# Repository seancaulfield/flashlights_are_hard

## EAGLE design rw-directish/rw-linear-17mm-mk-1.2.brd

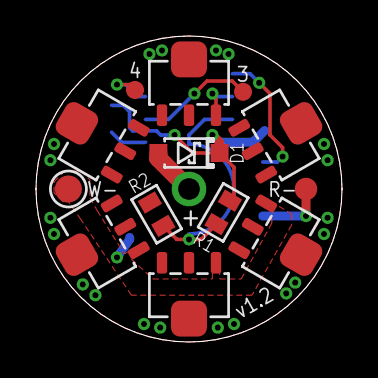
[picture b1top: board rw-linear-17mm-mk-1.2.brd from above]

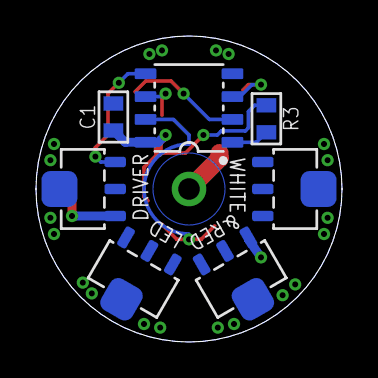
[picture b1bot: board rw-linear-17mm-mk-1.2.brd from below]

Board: 2 copper layers, 17.0 x 17.0 mm, 22 parts (7 on the bottom side), 11 nets.

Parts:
3, 4: M01SMD-1MM-DIA-NS; 1X01-SMD-1MM-DIA-NS
+: M01PTH-1.2MM-NS; 1X01-1.2MM-NS
C1: 1u; C0603-TIGHTER
D1: BAT165; SOD123-SCHOTTKY
FRAME1: FRAME-LETTERNO_PACKAGE; DUMMY
R1: 19K; R0603-TIGHTER
R2: 4K7; R0603-TIGHTER
R3: 10K; R0603-TIGHTER
R-: M01SMD-1.25MM-DIA; 1X01-SMD-1.25MM-DIA-NS
U0: Tiny13; SO08-NARROWER
U1, U2, U3, U4, U5, U6, U7, U8, U9, U10: AMC7135; SOT89-NOTHERM-ROUNDED
W-: M01SMD-1.5MM-DIA-NS; 1X01-SMD-1.5MM-DIA-NS

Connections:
3: 3.P$1, U0.2
4: 4.P$1, U0.3
BATT_DIV: R1.1, R2.2, U0.7
GND: C1.2, R2.1, U0.4, U1.4@1, U1.4@2, U2.4@1, U2.4@2, U3.4@1, U3.4@2, U4.4@1, U4.4@2, U5.4@1, U5.4@2, U6.4@1, U6.4@2, U7.4@1, U7.4@2, U8.4@1, U8.4@2, U9.4@1, U9.4@2, U10.4@1, U10.4@2
unnamed: R3.1, U0.1
PWM_R: U0.5, U10.3
PWM_W: U0.6, U1.3, U2.3, U3.3, U4.3, U5.3, U6.3, U7.3, U8.3, U9.3
RED_K: R-.P$1, U10.1
VBAT: +.P$1, D1.A
VCC: C1.1, D1.C, R1.2, R3.2, U0.8
WHITE_K: U1.1, U2.1, U3.1, U4.1, U5.1, U6.1, U7.1, U8.1, U9.1, W-.P$1

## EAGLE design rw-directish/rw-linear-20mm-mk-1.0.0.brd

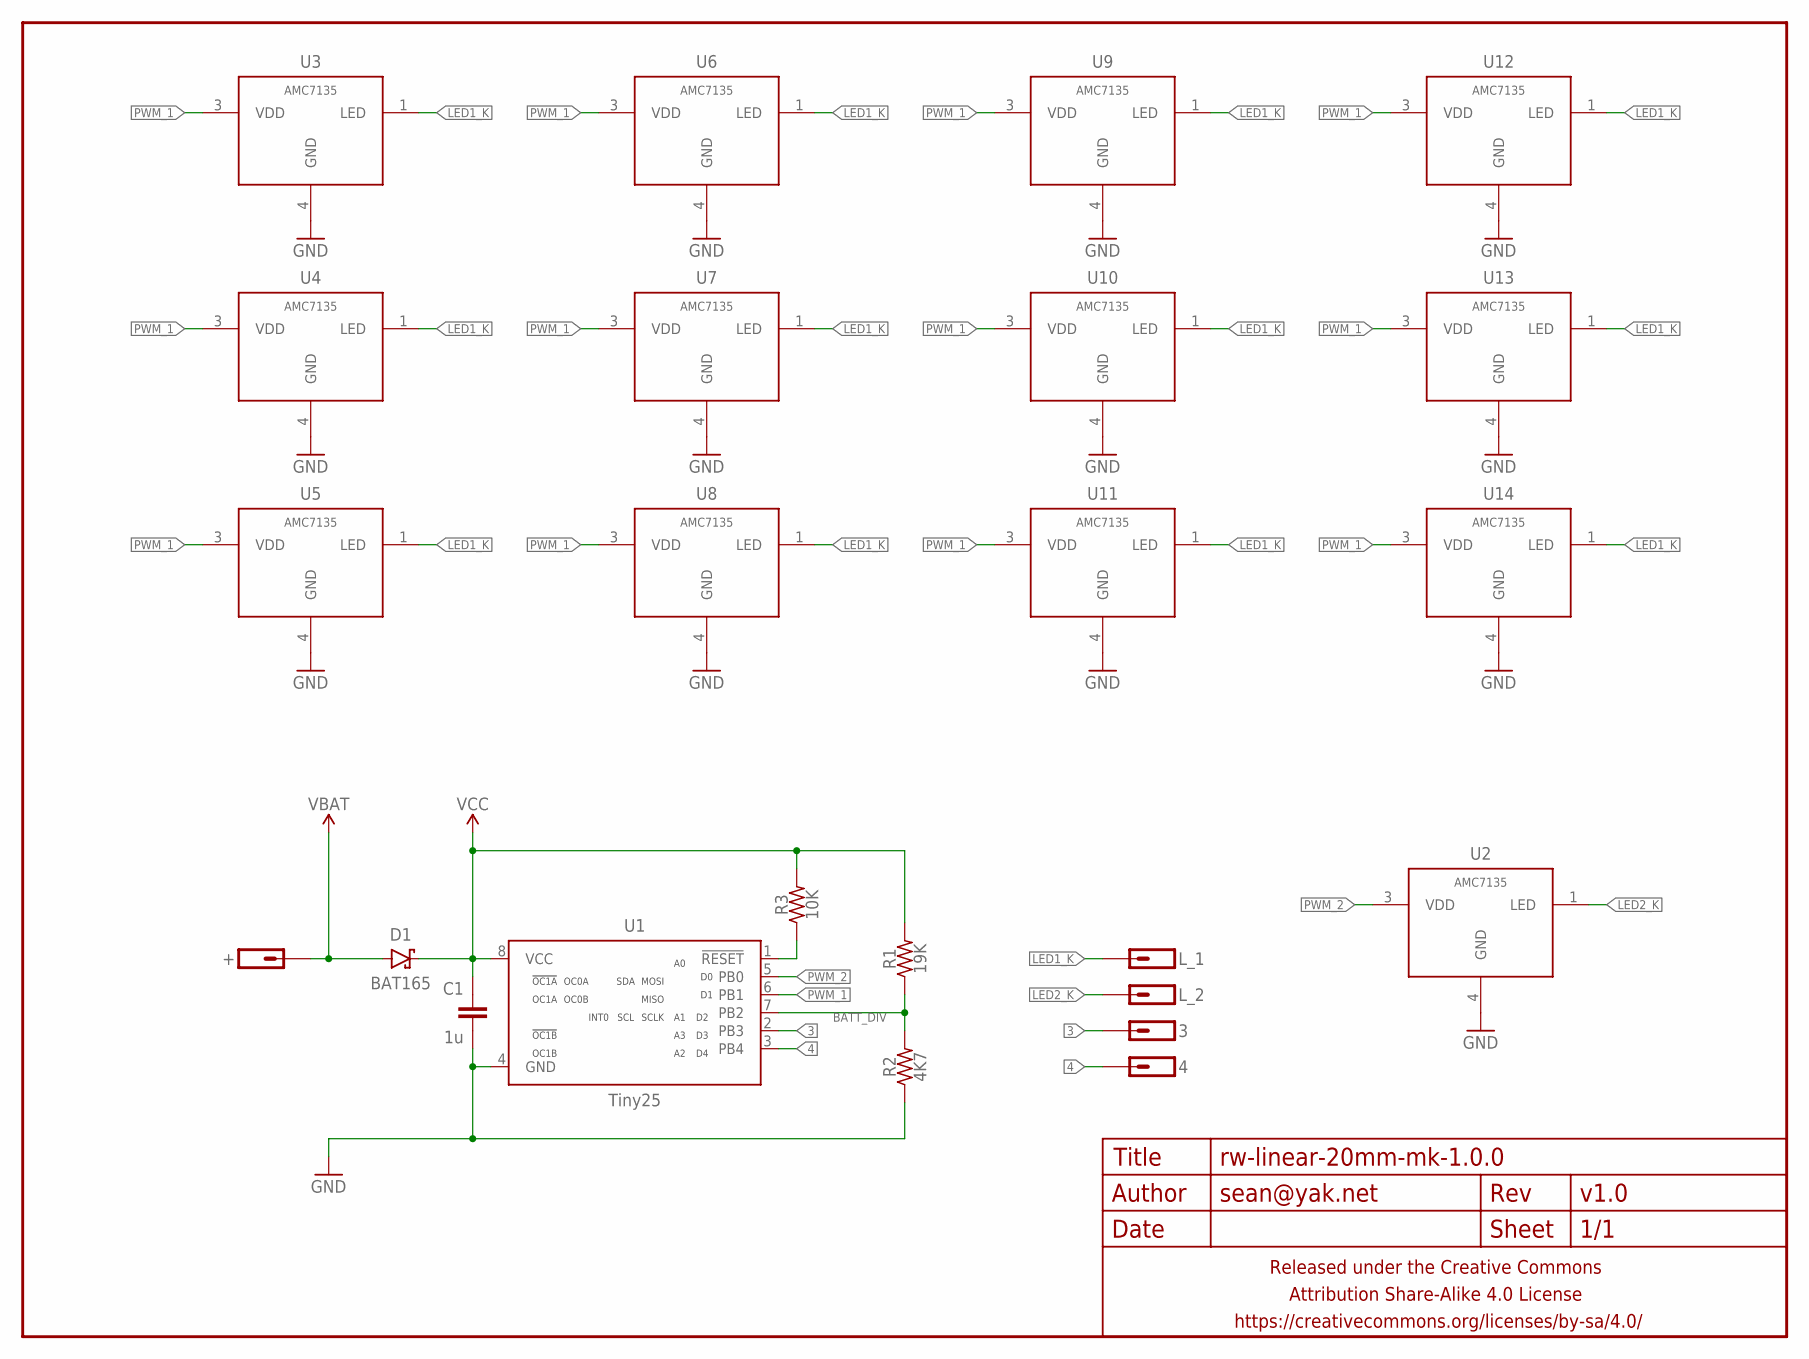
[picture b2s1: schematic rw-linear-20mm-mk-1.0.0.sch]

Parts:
3, 4: M01SMD-1MM-DIA-NS; 1X01-SMD-1MM-DIA-NS
+: M01PTH-1MM-CIR-NS; 1X01-1MM-CIR-NS
C1: 1u; C0603-TIGHTER
D1: BAT165; SMA-DIODE-SCHOTTKY
FRAME1: FRAME-LETTERNO_PACKAGE; DUMMY
L_1: M011X01-0.9MM-CIR; 1X01-0.9MM-CIR
L_2: M01PTH-0.8MM-CIR; 1X01-0.8MM-CIR
R1: 19K; R0603-TIGHTER
R2: 4K7; R0603-TIGHTER
R3: 10K; R0603-TIGHTER
U1: Tiny25; SO08-NARROWER
U2, U3, U4, U5, U6, U7, U8, U9, U10, U11, U12, U13, U14: AMC7135; SOT89-NOTHERM-ROUNDED-LESS

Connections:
3: 3.P$1, U1.2 (PB3)
4: 4.P$1, U1.3 (PB4)
BATT_DIV: R1.1, R2.2, U1.7 (PB2)
GND: C1.2, R2.1, U1.4 (GND), U2.4 (GND), U3.4 (GND), U4.4 (GND), U5.4 (GND), U6.4 (GND), U7.4 (GND), U8.4 (GND), U9.4 (GND), U10.4 (GND), U11.4 (GND), U12.4 (GND), U13.4 (GND), U14.4 (GND)
LED1_K: L_1.P$1, U3.1 (LED), U4.1 (LED), U5.1 (LED), U6.1 (LED), U7.1 (LED), U8.1 (LED), U9.1 (LED), U10.1 (LED), U11.1 (LED), U12.1 (LED), U13.1 (LED), U14.1 (LED)
LED2_K: L_2.1, U2.1 (LED)
unnamed: R3.1, U1.1 (!RESET)
PWM_1: U1.6 (PB1), U3.3 (VDD), U4.3 (VDD), U5.3 (VDD), U6.3 (VDD), U7.3 (VDD), U8.3 (VDD), U9.3 (VDD), U10.3 (VDD), U11.3 (VDD), U12.3 (VDD), U13.3 (VDD), U14.3 (VDD)
PWM_2: U1.5 (PB0), U2.3 (VDD)
VBAT: +.1, D1.A
VCC: C1.1, D1.C, R1.2, R3.2, U1.8 (VCC)

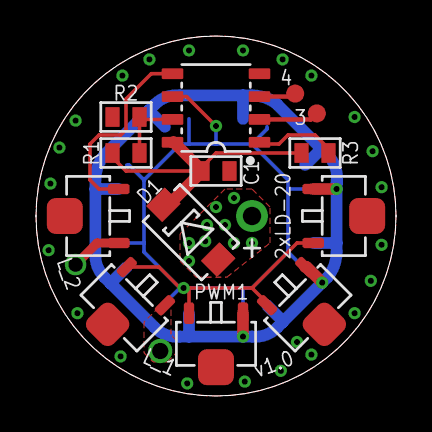
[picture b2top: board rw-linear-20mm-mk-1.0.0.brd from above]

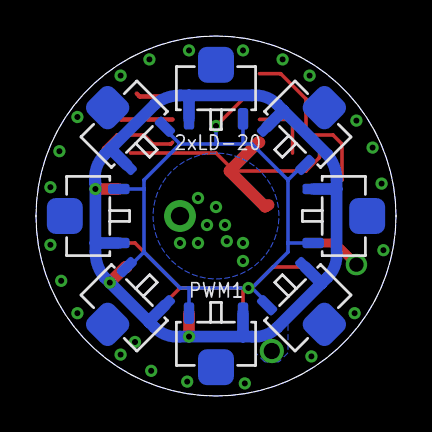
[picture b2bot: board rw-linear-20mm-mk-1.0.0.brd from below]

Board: 2 copper layers, 20.0 x 20.0 mm, 25 parts (8 on the bottom side), 11 nets.

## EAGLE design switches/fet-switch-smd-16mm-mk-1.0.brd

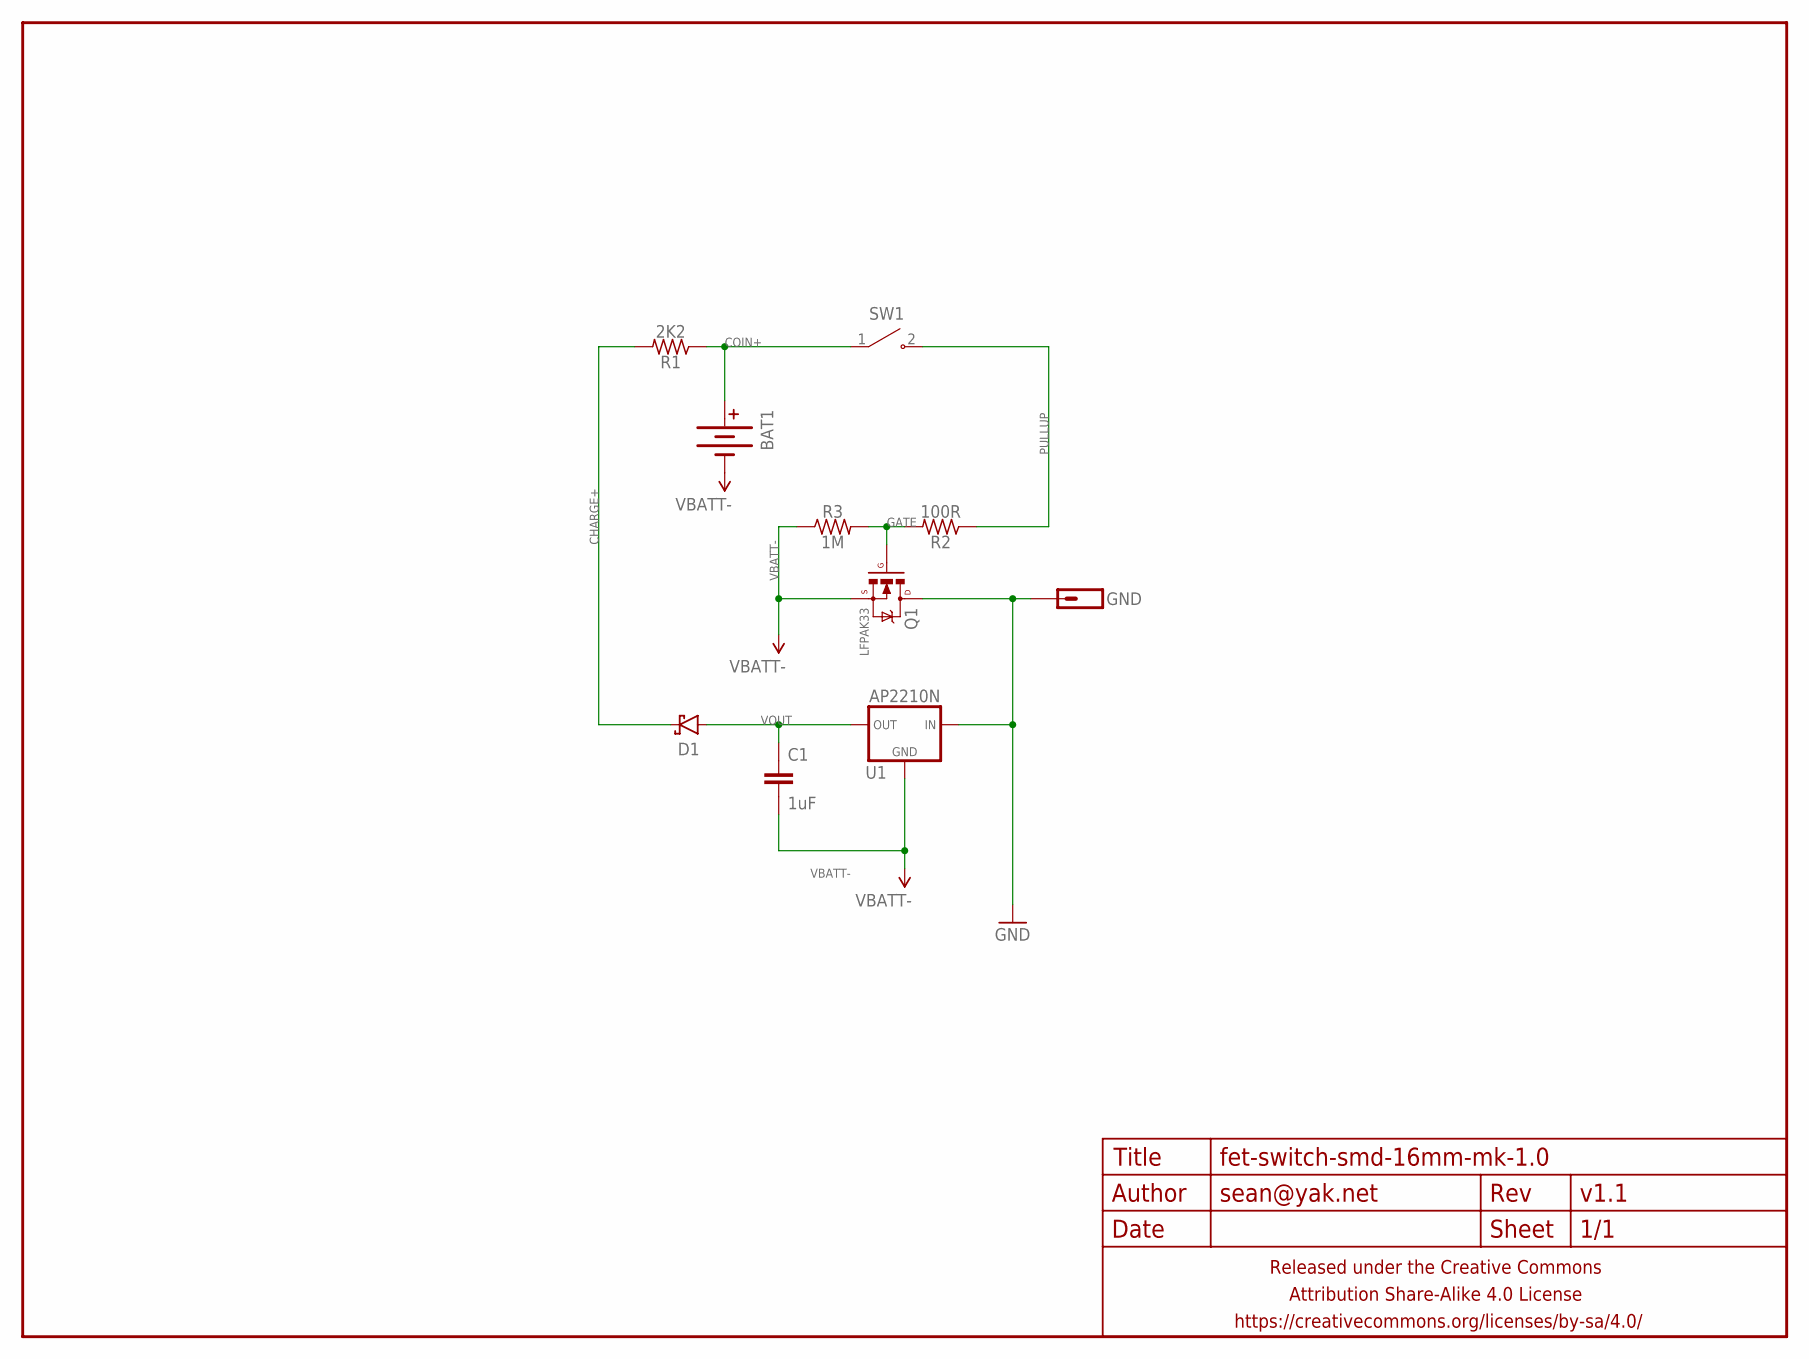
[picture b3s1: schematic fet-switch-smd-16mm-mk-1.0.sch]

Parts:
BAT1: BATTERYML414; BATTCON_4.8MM
C1: 1uF; C0402
D1: DIODE-SCHOTTKYSOD323; SOD323-SCHOTTKY
FRAME1: FRAME-LETTERNO_PACKAGE; DUMMY
GND: M01NOT-A-VIA-NOPE; 1X01_NOSILK_NOSTOP
Q1: LFPAK33
R1: 2K2; R0402
R2: 100R; R0402
R3: 1M; R0402
SW1: SWITCH-SPSTOMTEN-1288-SMD-NS; OMTEN-1288-LESS2-NS
U1: AP2210N; SOT23-TIGHTER

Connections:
CHARGE+: D1.C, R1.2
COIN+: BAT1.A1 (+), BAT1.A2 (+), R1.1, SW1.1 (COM)
GATE: Q1.4 (G), R2.2, R3.2
GND: GND.P$1, Q1.PAD (D), U1.3 (IN)
PULLUP: R2.1, SW1.2 (NO)
VBATT-: BAT1.-, C1.2, Q1.1 (S), Q1.2 (S), Q1.3 (S), R3.1, U1.1 (GND)
VOUT: C1.1, D1.A, U1.2 (OUT)

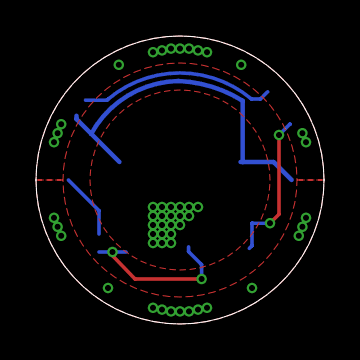
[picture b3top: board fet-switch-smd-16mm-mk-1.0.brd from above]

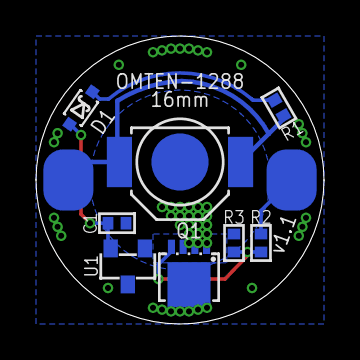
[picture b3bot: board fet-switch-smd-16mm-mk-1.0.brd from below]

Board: 2 copper layers, 16.0 x 16.0 mm, 11 parts (10 on the bottom side), 7 nets.

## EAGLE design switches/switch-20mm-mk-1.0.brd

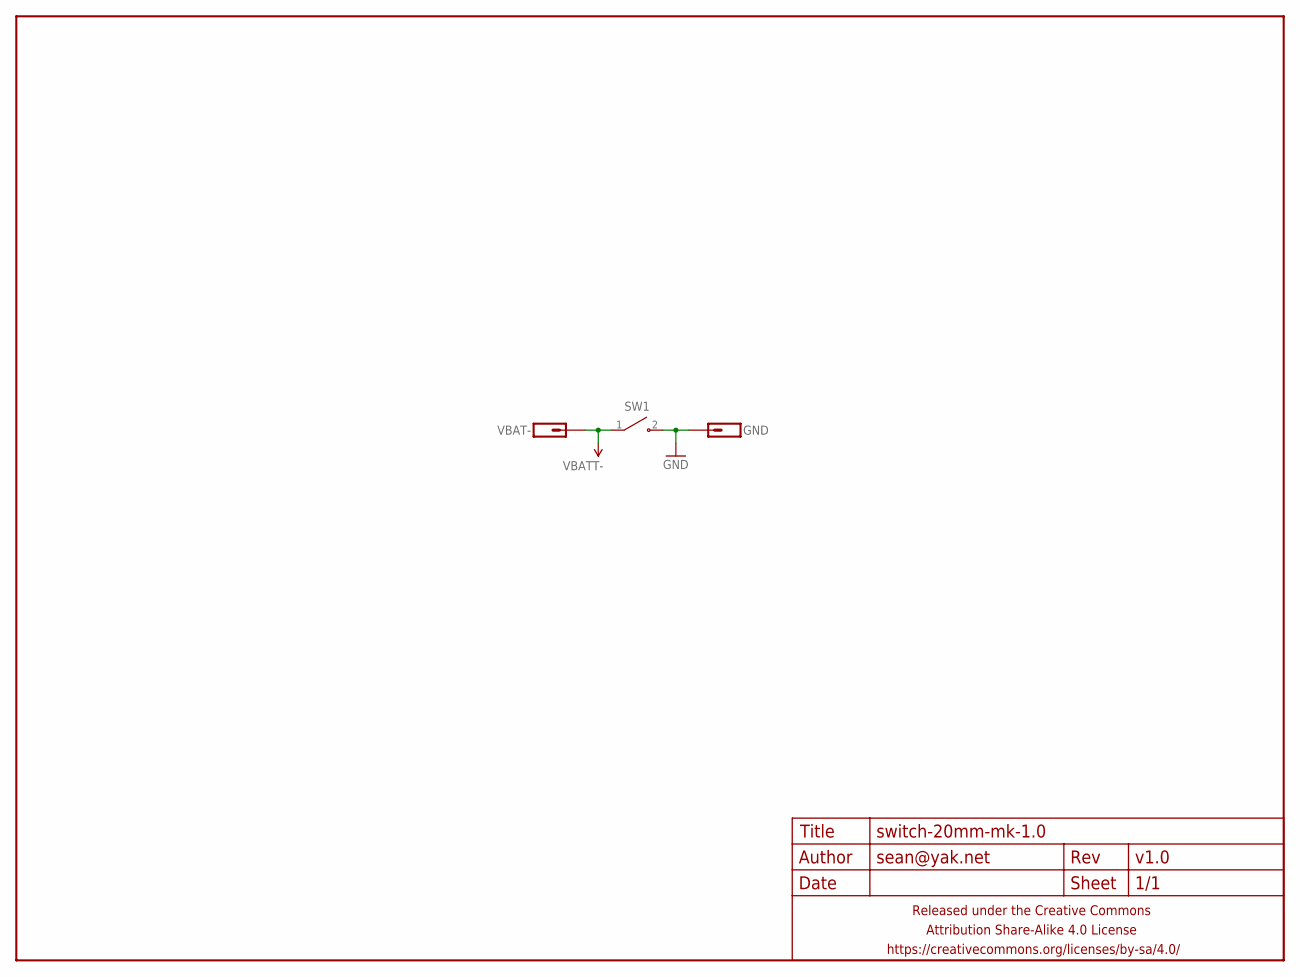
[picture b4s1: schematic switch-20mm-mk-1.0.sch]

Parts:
FRAME1: FRAME-LETTERNO_PACKAGE; DUMMY
GND: M01NOT-A-VIA-NOPE; 1X01_NOSILK_NOSTOP
SW1: SWITCH-SPSTOMTEN-1288-PTH; OMTEN-1288-PTH
VBAT-: M01PTH-1MM-CIR-NS; 1X01-1MM-CIR-NS

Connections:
GND: GND.P$1, SW1.2 (NO)
VBAT: SW1.1 (COM), VBAT-.1

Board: 2 copper layers, 4 parts (2 on the bottom side), 2 nets, no tracks yet.

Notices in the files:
parts and their libraries:
a_parts: Released under the Creative Commons Attribution Share-Alike 4.0 License
a_parts: https://creativecommons.org/licenses/by-sa/4.0
a_parts: Released under the Creative Commons
